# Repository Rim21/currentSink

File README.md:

# currentSink
1st PCB project building a current sink with uController interface

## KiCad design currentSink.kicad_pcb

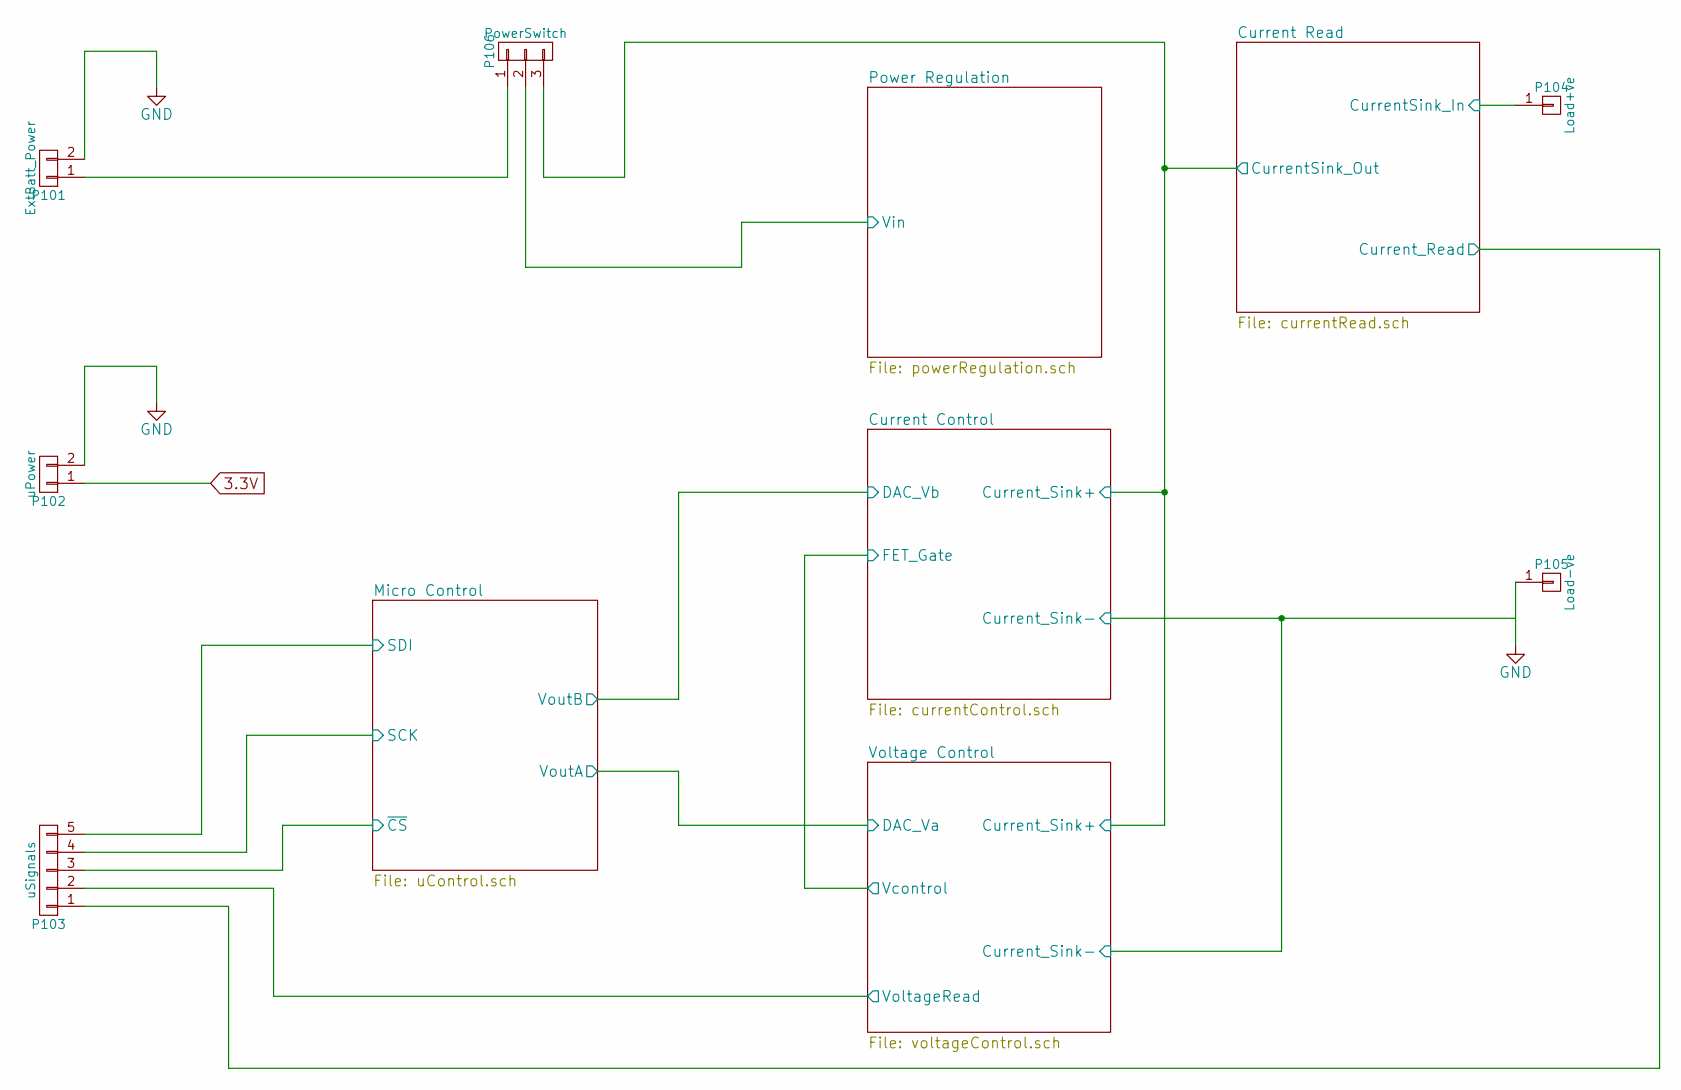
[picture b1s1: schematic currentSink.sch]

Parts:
P101: ExtBatt_Power; Pin_Header_Straight_1x02
P102: uPower; Pin_Header_Straight_1x02; MPN Value
P103: uSignals; Pin_Header_Straight_1x05
P104: Load+ve; 1pin
P105: Load-ve; 1pin
P106: PowerSwitch; Pin_Header_Straight_1x03

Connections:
3.3V: P102.1; also elsewhere on the board
/Current Read/CurrentSink_In: P104.1; also elsewhere on the board
/Current Read/CurrentSink_Out: P106.3; also elsewhere on the board
/Current Read/Current_Read: P103.1; also elsewhere on the board
/Micro Control/SCK: P103.4; also elsewhere on the board
/Micro Control/SDI: P103.5; also elsewhere on the board
/Micro Control/~CS: P103.3; also elsewhere on the board
/Power Regulation/Vin: P106.2; also elsewhere on the board
/Voltage Control/VoltageRead: P103.2; also elsewhere on the board
GND: P101.2, P102.2, P105.1; also elsewhere on the board
unnamed: P101.1, P106.1

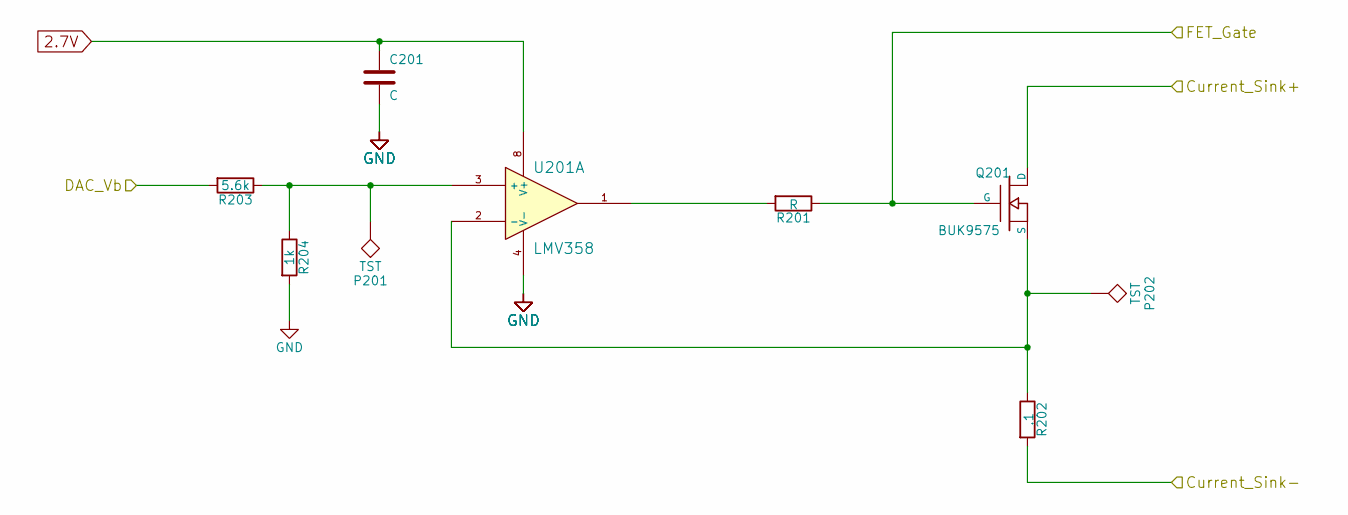
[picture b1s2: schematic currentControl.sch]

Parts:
C201: C; C_0805_HandSoldering
P201, P202: TST; Measurement_Point_Round-TH_Small
Q201: BUK9575; TO-220_FET-GDS_Vertical; MPN BUK9575-100A,127
R201: R; R_0805_HandSoldering
R202: .1; Resistor_Horizontal_RM15mm; MPN AC01000001007JA100
R203: 5.6k; R_0805_HandSoldering; MPN Value
R204: 1k; R_0805_HandSoldering; MPN Value
U201: LMV358; SOIC-8-N

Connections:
2.7V: C201.1, U201.8 (V+); also elsewhere on the board
/Current Control/Current_Sink-: R202.2; also elsewhere on the board
/Current Control/DAC_Vb: R203.2; also elsewhere on the board
/Current Control/FET_Gate: Q201.G, R201.1; also elsewhere on the board
/Current Read/CurrentSink_Out: Q201.D; also elsewhere on the board
GND: C201.2, R204.2, U201.4 (V-); also elsewhere on the board
unnamed 18: P201.1, R203.1, R204.1, U201.3 (+); also elsewhere on the board
unnamed: P202.1, Q201.S, R202.1, U201.2 (-)
unnamed: R201.2, U201.1

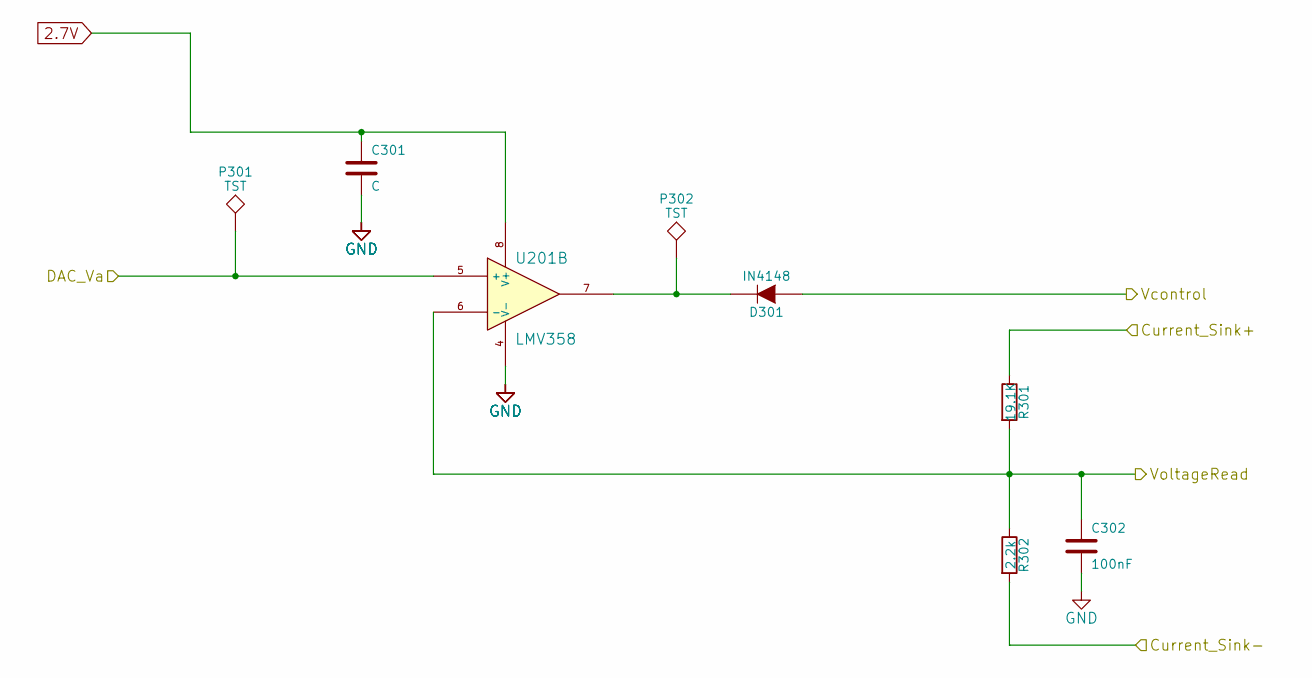
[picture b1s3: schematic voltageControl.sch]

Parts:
C301: C; C_0805_HandSoldering
C302: 100nF; C_0805_HandSoldering; MPN Value
D301: IN4148; SOD-523; MPN 1N4148WT-7
P301, P302: TST; Measurement_Point_Round-TH_Small
R301: 19.1K; R_0805_HandSoldering
R302: 2.2k; R_0805_HandSoldering
U201: LMV358; SOIC-8-N

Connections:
2.7V: C301.1, U201.8 (V+); also elsewhere on the board
/Current Control/Current_Sink-: R302.2; also elsewhere on the board
/Current Control/FET_Gate: D301.1 (A); also elsewhere on the board
/Current Read/CurrentSink_Out: R301.1; also elsewhere on the board
/Voltage Control/DAC_Va: P301.1, U201.5 (+); also elsewhere on the board
/Voltage Control/VoltageRead: C302.1, R301.2, R302.1, U201.6 (-); also elsewhere on the board
GND: C301.2, C302.2, U201.4 (V-); also elsewhere on the board
unnamed: D301.2 (K), P302.1, U201.7

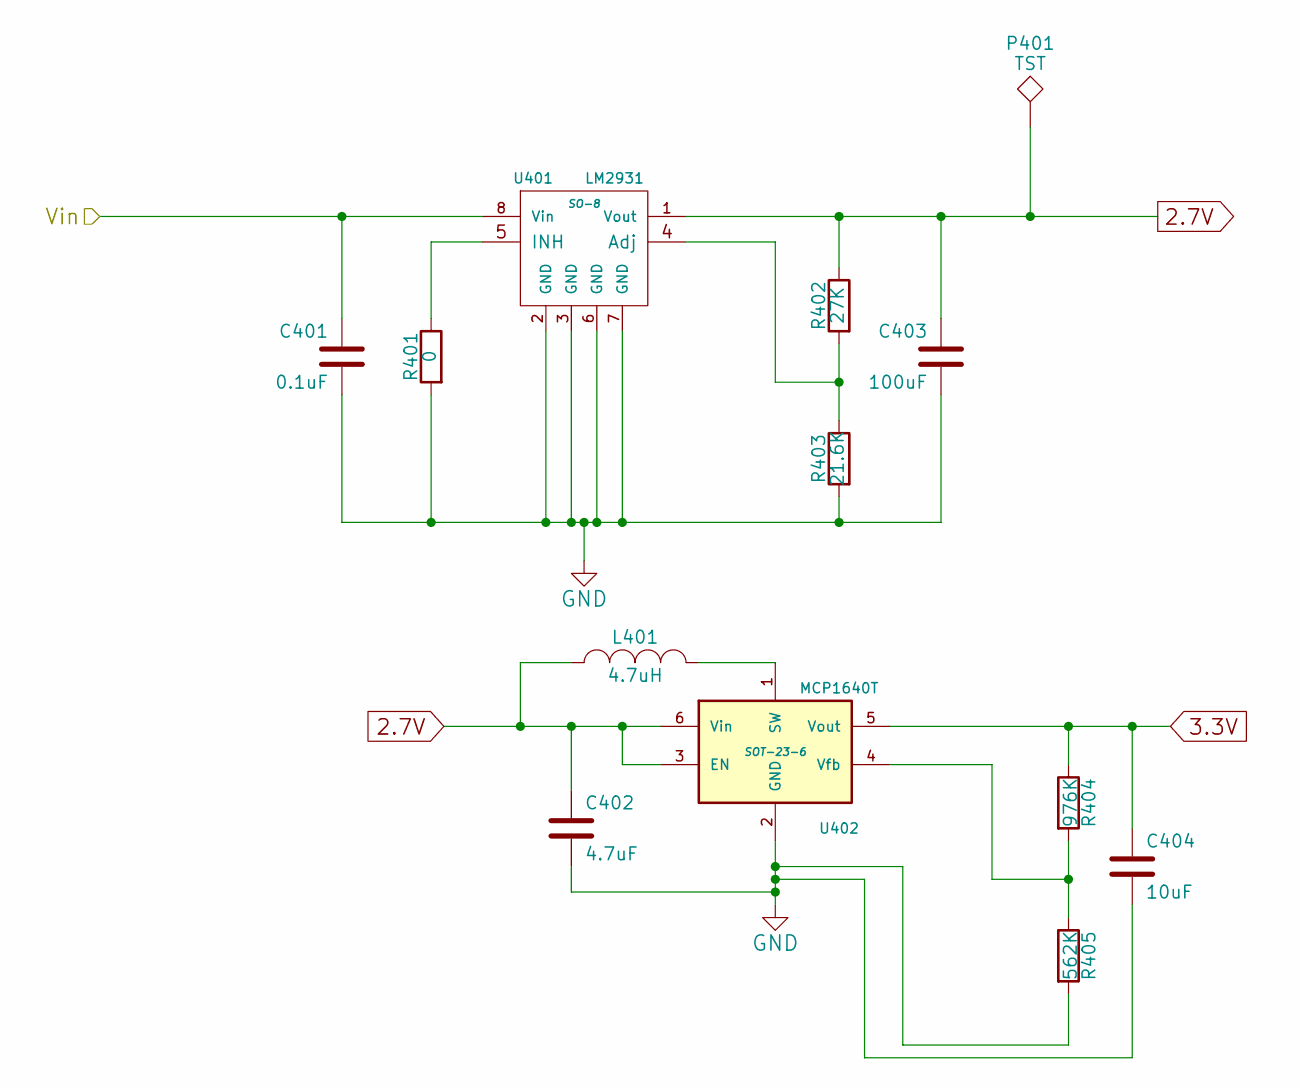
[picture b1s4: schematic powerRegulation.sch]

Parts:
C401: 0.1uF; C_0805_HandSoldering
C402: 4.7uF; C_0805_HandSoldering; MPN Value
C403: 100uF; C_0805_HandSoldering
C404: 10uF; C_0805_HandSoldering
L401: 4.7uH; R_0805_HandSoldering; MPN AIML-0805HC-4R7M-T
P401: TST; Measurement_Point_Round-TH_Small
R401: 0; R_0805_HandSoldering
R402: 27K; R_0805_HandSoldering
R403: 21.6K; R_0805_HandSoldering
R404: 976K; R_0805_HandSoldering
R405: 562K; R_0805_HandSoldering
U401: LM2931; SO-8
U402: MCP1640T; SOT-23-6

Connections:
2.7V: C402.1, C403.1, L401.1, P401.1, R402.1, U401.1 (Vout), U402.3 (EN), U402.6 (Vin); also elsewhere on the board
3.3V: C404.1, R404.1, U402.5 (Vout); also elsewhere on the board
/Power Regulation/Vin: C401.1, U401.8 (Vin); also elsewhere on the board
GND: C401.2, C402.2, C403.2, C404.2, R401.2, R403.2, R405.2, U401.2 (GND), U401.3 (GND), U401.6 (GND), U401.7 (GND), U402.2 (GND); also elsewhere on the board
unnamed: L401.2, U402.1 (SW)
unnamed: R401.1, U401.5 (INH)
unnamed: R402.2, R403.1, U401.4 (Adj)
unnamed: R404.2, R405.1, U402.4 (Vfb)

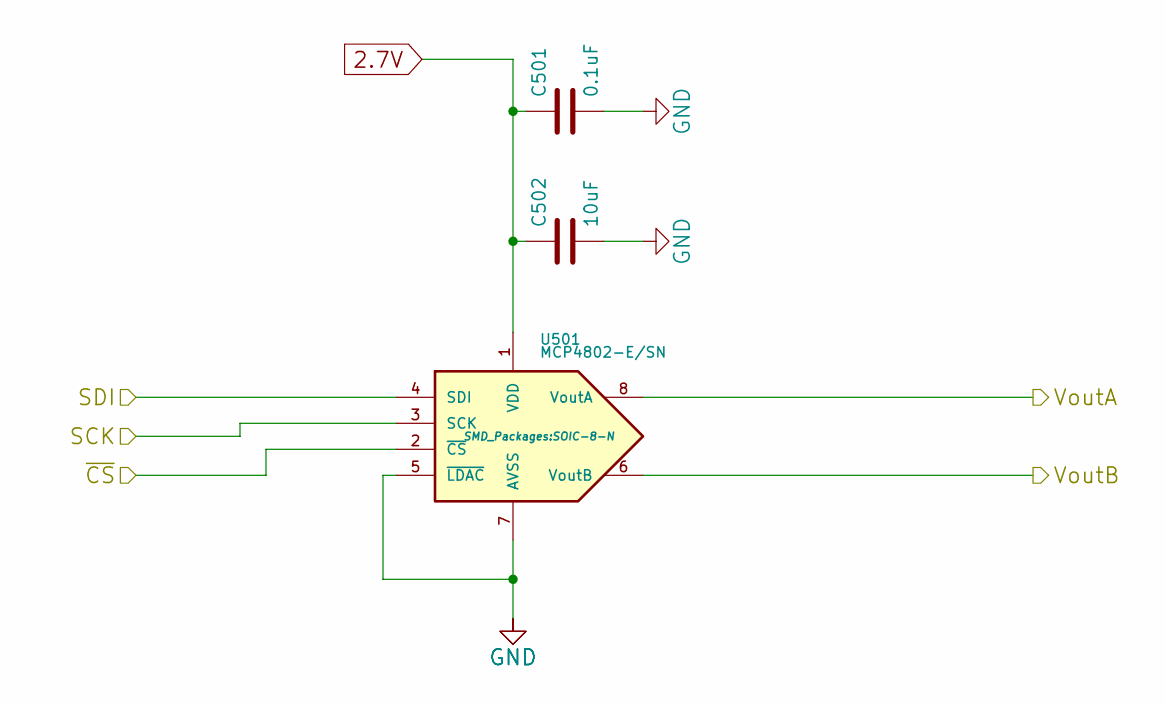
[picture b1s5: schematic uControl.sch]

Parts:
C501: 0.1uF; C_0805_HandSoldering
C502: 10uF; C_0805_HandSoldering; MPN Value
U501: MCP4802-E/SN; SOIC-8-N

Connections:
2.7V: C501.1, C502.1, U501.1 (VDD); also elsewhere on the board
/Current Control/DAC_Vb: U501.6 (VoutB); also elsewhere on the board
/Micro Control/SCK: U501.3 (SCK); also elsewhere on the board
/Micro Control/SDI: U501.4 (SDI); also elsewhere on the board
/Micro Control/~CS: U501.2 (~CS~); also elsewhere on the board
/Voltage Control/DAC_Va: U501.8 (VoutA); also elsewhere on the board
GND: C501.2, C502.2, U501.5 (~LDAC~), U501.7 (AVSS); also elsewhere on the board

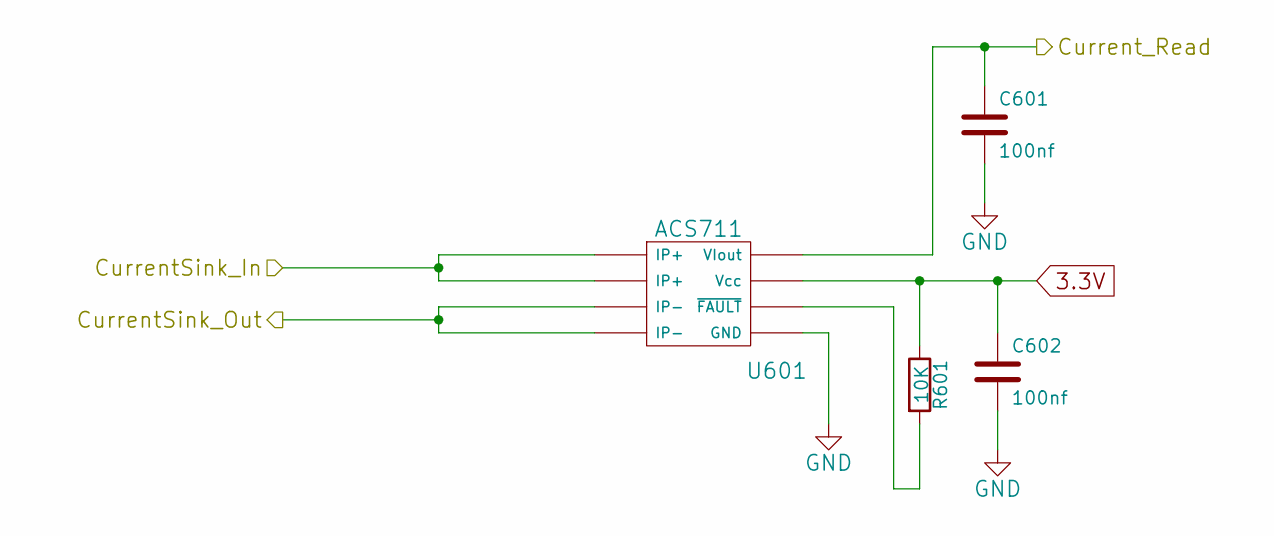
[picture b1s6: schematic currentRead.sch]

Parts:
C601, C602: 100nf; C_0805_HandSoldering; MPN Value
R601: 10K; R_0805_HandSoldering
U601: ACS711; SOIC-8-N; MPN ACS711KLCTR-12AB-T

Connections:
3.3V: C602.1, R601.1, U601.8 (Vcc); also elsewhere on the board
/Current Read/CurrentSink_In: U601.1 (IP+), U601.2 (IP+); also elsewhere on the board
/Current Read/CurrentSink_Out: U601.3 (IP-), U601.4 (IP-); also elsewhere on the board
/Current Read/Current_Read: C601.1, U601.7 (VIout); also elsewhere on the board
GND: C601.2, C602.2, U601.5 (GND); also elsewhere on the board
unnamed: R601.2, U601.6 (~FAULT)

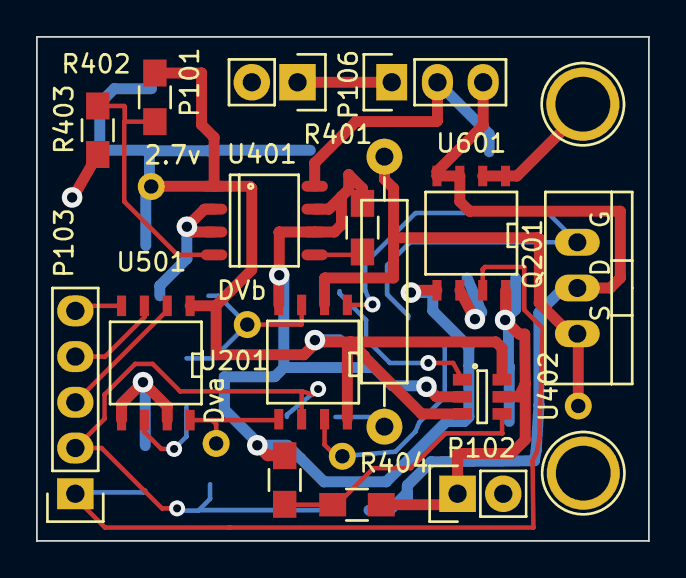
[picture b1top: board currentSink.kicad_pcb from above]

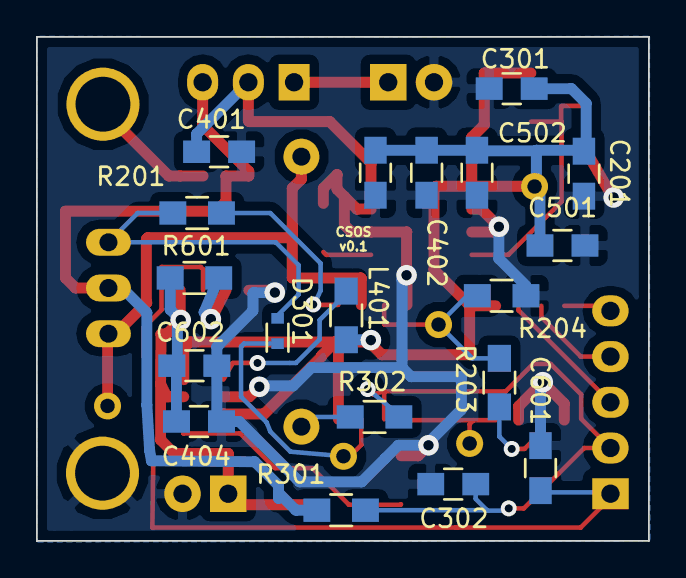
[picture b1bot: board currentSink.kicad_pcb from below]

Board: 2 copper layers, 34.0 x 28.0 mm, 42 parts (19 on the bottom side), 25 nets.

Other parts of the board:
2.7v: TST; Measurement_Point_Round-TH_Small
DVb: TST; Measurement_Point_Round-TH_Small
Dva: TST; Measurement_Point_Round-TH_Small

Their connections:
2.7V: 2.7v.1; also elsewhere on the board
/Voltage Control/DAC_Va: Dva.1; also elsewhere on the board
unnamed 18: DVb.1; also elsewhere on the board

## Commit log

2015-04-05 Kicad project file creation
2015-04-05 adding preliminary schematic
2015-04-05 updated schematic with MCP4802 and added datasheets
2015-04-05 added LM2931D-R regulator
2015-04-05 updated project file
2015-04-05 added new sheets currentControl, powerRegulatio, uControl and voltageControl
2015-04-05 updated schematic with current read
2015-04-06 added additional regulator to power the ACS711 and potentially a micro at 3.3V
2015-04-06 updated schematic to include a switch for use of an external power source to the circuit
2015-04-06 updated power regulation circuit with a different component so that the pin numbers now show
2015-04-06 updated with association labels
2015-04-06 updated with a netlist
2015-04-06 updated schematic with corrected wiring after all passives became disconnected
2015-04-07 deleted duplicated CSOS schematics
2015-04-07 tried using git rm to remove the unwanted pdfs
2015-04-07 added CSOS_Schmatic file
2015-04-07 changed the IC filename pdfs
2015-04-09 updated current control circuit with voltage divider to increase resolution to 12mA
2015-04-11 updated project with most footprint associations
2015-04-11 association of footprints complete
2015-04-11 removed duplicates and bad wire connections to enable the generation of a PCB
2015-04-12 initial layout complete with gnd plane
2015-04-12 updated with some of the frontside tracks
2015-04-13 updated layout - note not optimised
2015-04-13 updated layout. DRC has 4 footprint errors for U402 however measurements appear OK to datasheet
2015-04-14 reduced board six to 34mm
2015-04-14 adjusted board sixe to 34mm x 28mm
2015-04-15 adding .gitignore
2015-04-15 updated gitignore file with additional file extensions
2015-04-15 added gerber files that have been submitted
2015-04-18 updated schematic with part numbers to ICs
